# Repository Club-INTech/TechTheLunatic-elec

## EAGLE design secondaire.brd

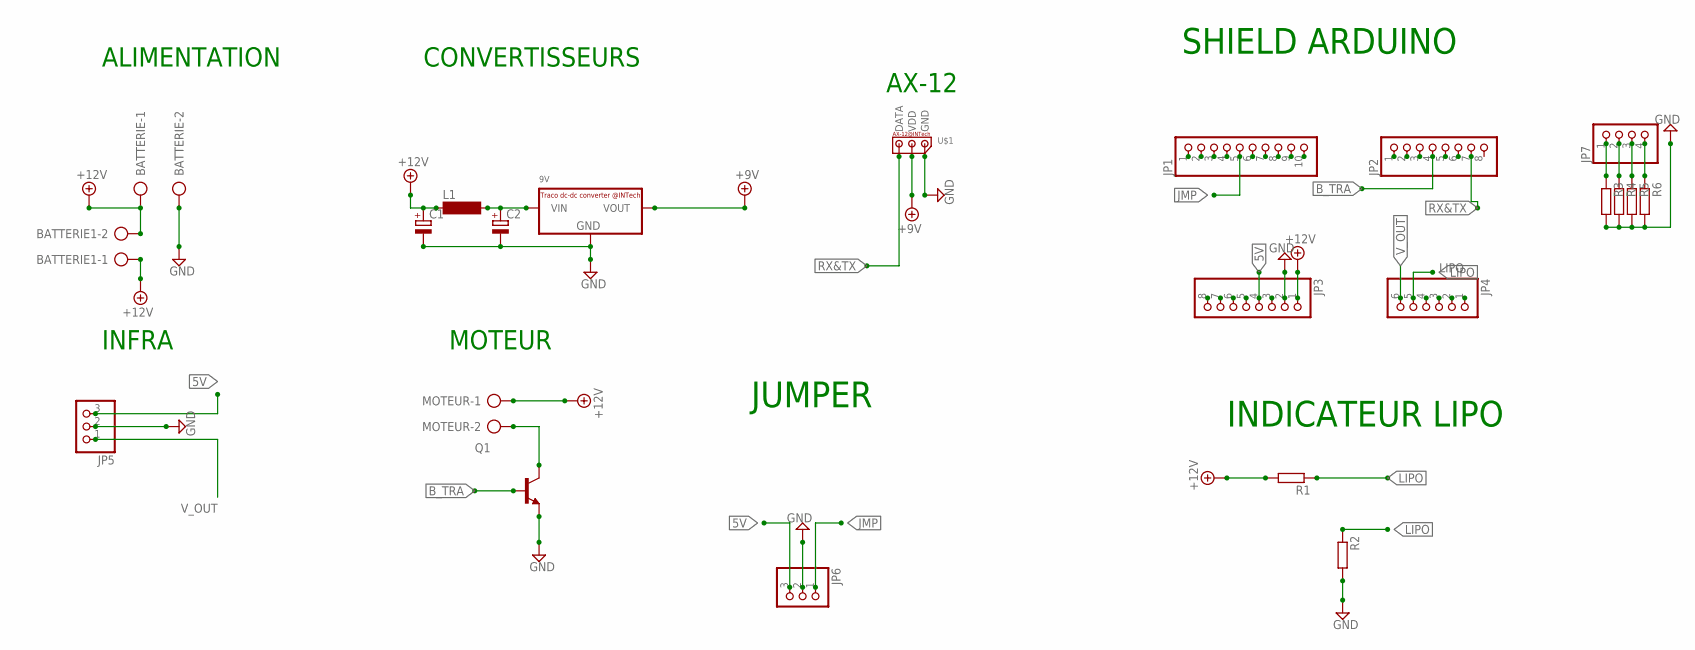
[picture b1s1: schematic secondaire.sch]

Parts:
9V: R-78C-1.0_INTECH; SIP3_INTECH
BATTERIE, BATTERIE1: AK300/2
C1, C2: CPOL-EUE2.5-6; E2,5-6
JP1: PINHD-1X10; 1X10
JP2, JP3: PINHD-1X8; 1X08
JP4: PINHD-1X6; 1X06
JP5, JP6: PINHD-1X3; 1X03
JP7: PINHD-1X4; 1X04
L1: SD12-1000; SD12_1000
MOTEUR: AK300/2
Q1: BC237-NPN-TO92-CBE; TO92-CBE
R1, R2, R3, R4, R5, R6: R-EU_0204/7; 0204/7
U$1: AX-12_CF_INTECH

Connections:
5V: JP3.4, JP5.3, JP6.3
+9V: 9V.VOUT, U$1.VDD
+12V: BATTERIE.1, BATTERIE1.1, BATTERIE1.2, C1.+, JP3.1, L1.1, MOTEUR.1, R1.2
B_TRA: JP2.4, Q1.B
COL: MOTEUR.2, Q1.C
GND: 9V.GND, BATTERIE.2, C1.-, C2.-, JP3.2, JP5.2, JP6.2, Q1.E, R2.2, R3.2, R4.2, R5.2, R6.2, U$1.GND
JMP: JP1.5, JP6.1
LIPO: JP4.5, R1.1, R2.1
unnamed: 9V.VIN, C2.+, L1.2
unnamed: JP7.1, R3.1
unnamed: JP7.2, R4.1
unnamed: JP7.3, R5.1
unnamed: JP7.4, R6.1
RX&TX: JP2.7, U$1.DATA
V_OUT: JP4.6, JP5.1

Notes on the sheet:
ALIMENTATION
CONVERTISSEURS
MOTEUR
AX-12
INFRA
JUMPER
SHIELD ARDUINO
INDICATEUR LIPO

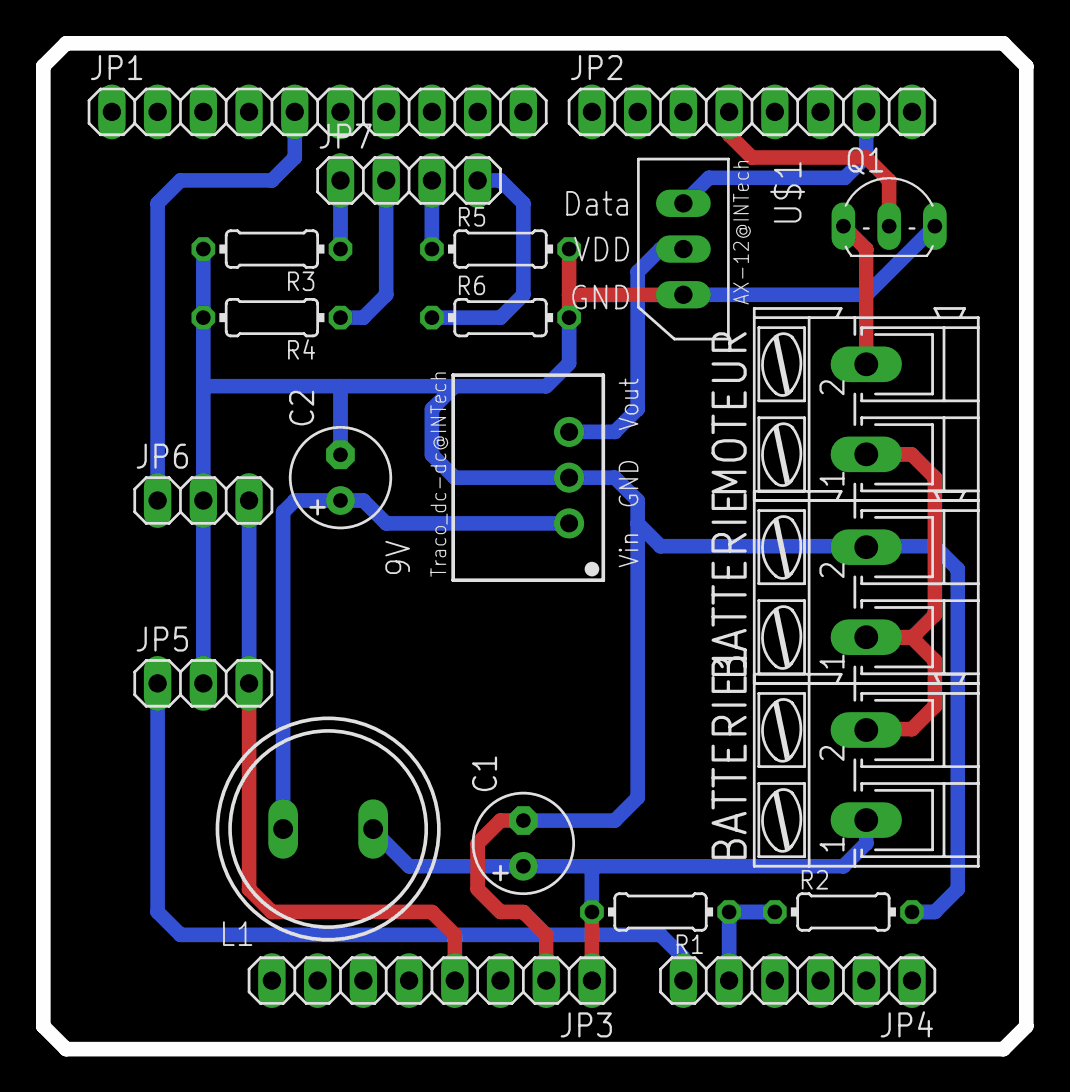
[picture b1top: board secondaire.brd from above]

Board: 2 copper layers, 54.6 x 55.9 mm, 22 parts (0 on the bottom side), 15 nets.

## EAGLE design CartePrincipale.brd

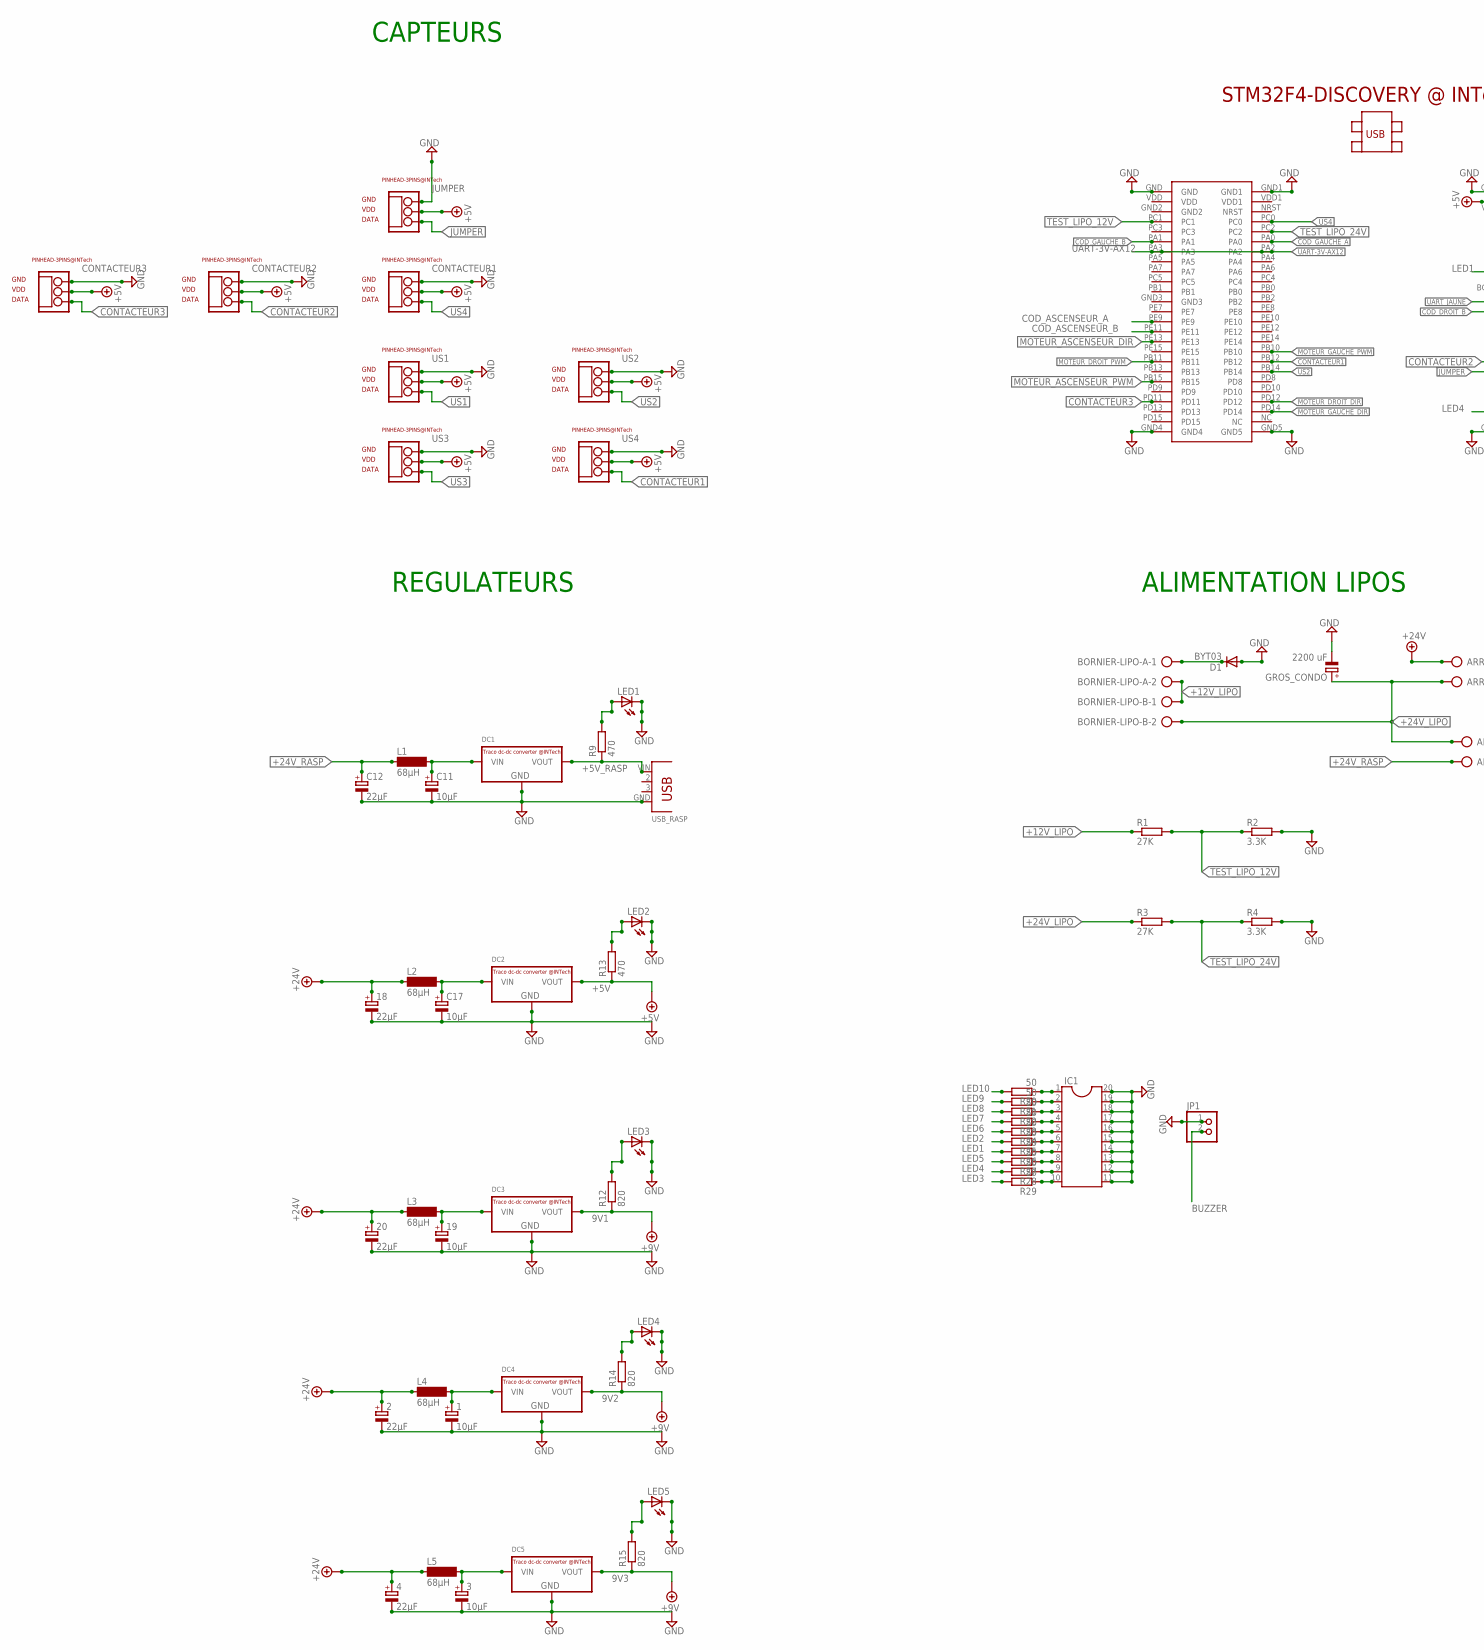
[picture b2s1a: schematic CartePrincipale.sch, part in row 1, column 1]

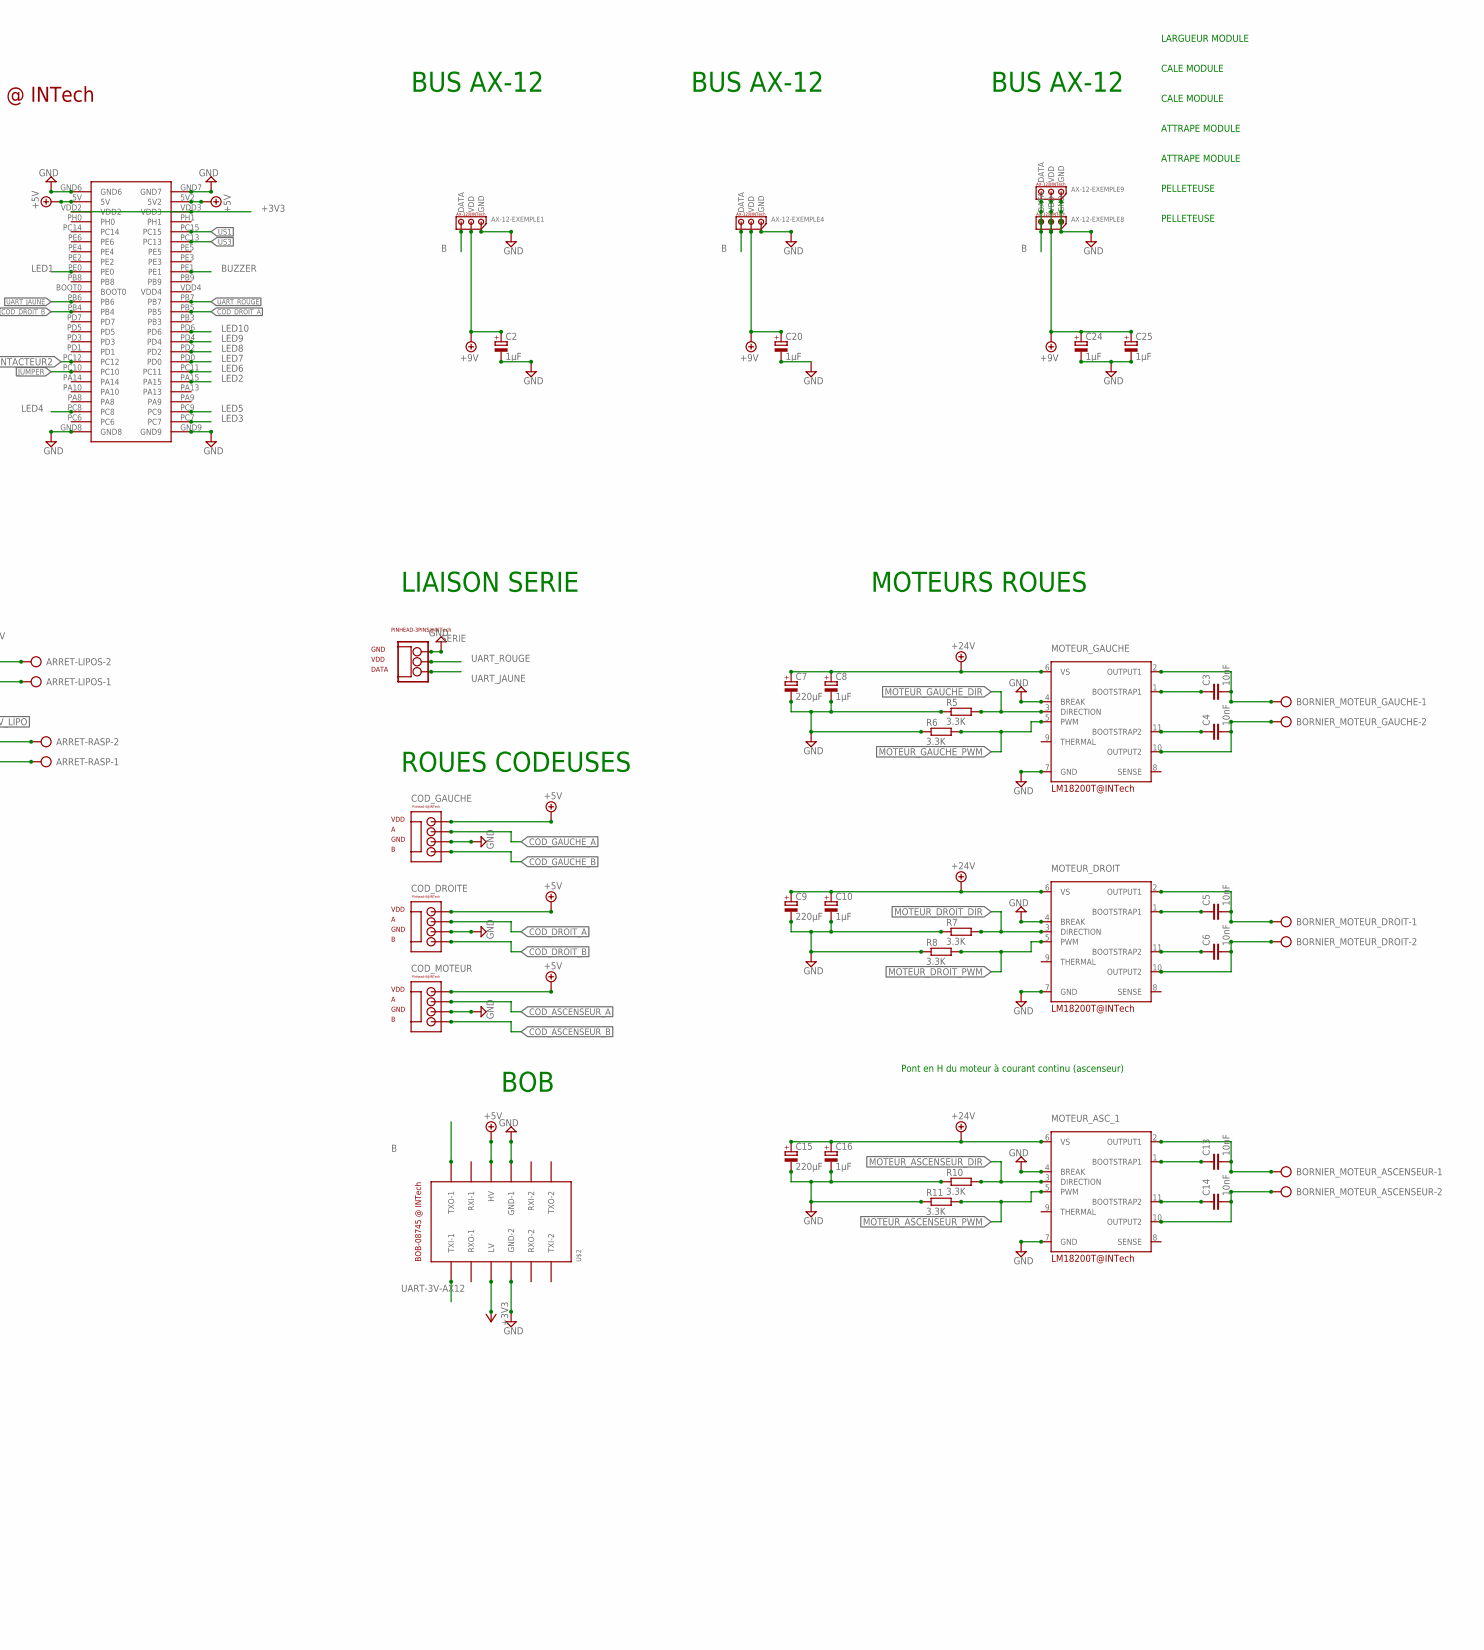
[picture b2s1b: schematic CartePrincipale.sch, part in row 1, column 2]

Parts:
1, 3, 19: 10µF; E2,5-6
2, 4, 18, 20: 22µF; E2,5-6
ARRET-LIPOS: AK300/2
ARRET-RASP: AK300/2
AX-12-EXEMPLE1, AX-12-EXEMPLE4, AX-12-EXEMPLE8, AX-12-EXEMPLE9: AX-12_CF_INTECH
BORNIER-LIPO-A: AK300/2
BORNIER-LIPO-B: AK300/2
BORNIER_MOTEUR_ASCENSEUR: AK300/2
BORNIER_MOTEUR_DROIT: AK300/2
BORNIER_MOTEUR_GAUCHE: AK300/2
C2, C20, C24, C25: 1µF; E2,5-6E
C3, C4, C5, C6, C13, C14: 10nF; C050-025X075
C7, C9, C15: 220µF; E3,5-8
C8, C10, C16: 1µF; E3,5-8
C11, C17: 10µF; E2,5-6
C12: 22µF; E2,5-6
COD_DROITE: PINHEAD-4_CF_INTECH
COD_GAUCHE: PINHEAD-4_CF_INTECH
COD_MOTEUR: PINHEAD-4_CF_INTECH
CONTACTEUR1, CONTACTEUR2, CONTACTEUR3: PINHEAD_CF_INTECH
D1: BYT03; DO27-15
DC1, DC2: 5V_1A; SIP3_INTECH
DC3, DC4, DC5: 9V_1A; SIP3_INTECH
GROS_CONDO: 2200 uF; EB20D
IC1: DIL20S; SOCKET-20
JP1: PINHD-1X2; 1X02
JUMPER: PINHEAD_CF_INTECH
L1, L2, L3, L4, L5: 68µH; SD12K100
LED1, LED2, LED3, LED4, LED5: LED5MM
MOTEUR_ASC_1: LM18200T_CF_INTECH
MOTEUR_DROIT: LM18200T_CF_INTECH
MOTEUR_GAUCHE: LM18200T_CF_INTECH
R1, R3: 27K; 0207/10
R2, R4, R5, R6, R7, R8, R10, R11: 3.3K; 0207/10
R9, R13: 470; 0207/10
R12, R14, R15: 820; 0207/10
R20, R21, R22, R23, R24, R25, R26, R27, R28, R29: 50; 0207/2V
SERIE: PINHEAD_CF_INTECH
U$1: STM32F4-DISCOVERY
U$2: BOB-08745
US1, US2, US3, US4: PINHEAD_CF_INTECH
USB_RASP: USB_87520; USB

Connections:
9V1: AX-12-EXEMPLE8.VDD, AX-12-EXEMPLE9.VDD, C24.+, C25.+, DC3.VOUT, R12.1
9V2: AX-12-EXEMPLE4.VDD, C20.+, DC4.VOUT, R14.1
9V3: AX-12-EXEMPLE1.VDD, C2.+, DC5.VOUT, R15.1
+3V3: U$1.VDD2, U$1.VDD3, U$2.LV
+5V: COD_DROITE.VDD, COD_GAUCHE.VDD, COD_MOTEUR.VDD, CONTACTEUR1.VDD, CONTACTEUR2.VDD, CONTACTEUR3.VDD, DC2.VOUT, JUMPER.VDD, R13.1, U$1.5V, U$1.5V2, U$2.HV, US1.VDD, US2.VDD, US3.VDD, US4.VDD
+5V_RASP: DC1.VOUT, R9.1, USB_RASP.VIN
+12V_LIPO: BORNIER-LIPO-A.2, BORNIER-LIPO-B.1, R1.1
+24V: 2.+, 4.+, 18.+, 20.+, ARRET-LIPOS.2, C7.+, C8.+, C9.+, C10.+, C15.+, C16.+, L2.1, L3.1, L4.1, L5.1, MOTEUR_ASC_1.6 (VS), MOTEUR_DROIT.6 (VS), MOTEUR_GAUCHE.6 (VS)
+24V_LIPO: ARRET-LIPOS.1, ARRET-RASP.2, BORNIER-LIPO-B.2, GROS_CONDO.+, R3.1
+24V_RASP: ARRET-RASP.1, C12.+, L1.1
B: AX-12-EXEMPLE1.DATA, AX-12-EXEMPLE4.DATA, AX-12-EXEMPLE8.DATA, AX-12-EXEMPLE9.DATA, U$2.TXO-1
BUZZER: JP1.2, U$1.PE1
COD_ASCENSEUR_A: COD_MOTEUR.A, U$1.PE9
COD_ASCENSEUR_B: COD_MOTEUR.B, U$1.PE11
COD_DROIT_A: COD_DROITE.A, U$1.PB5
COD_DROIT_B: COD_DROITE.B, U$1.PB4
COD_GAUCHE_A: COD_GAUCHE.A, U$1.PA0
COD_GAUCHE_B: COD_GAUCHE.B, U$1.PA1
CONTACTEUR1: U$1.PB12, US4.DATA
CONTACTEUR2: CONTACTEUR2.DATA, U$1.PC12
CONTACTEUR3: CONTACTEUR3.DATA, U$1.PD11
GND: 1.-, 2.-, 3.-, 4.-, 18.-, 19.-, 20.-, AX-12-EXEMPLE1.GND, AX-12-EXEMPLE4.GND, AX-12-EXEMPLE8.GND, AX-12-EXEMPLE9.GND, C2.-, C7.-, C8.-, C9.-, C10.-, C11.-, C12.-, C15.-, C16.-, C17.-, C20.-, C24.-, C25.-, COD_DROITE.GND, COD_GAUCHE.GND, COD_MOTEUR.GND, CONTACTEUR1.GND, CONTACTEUR2.GND, CONTACTEUR3.GND, D1.A, DC1.GND, DC2.GND, DC3.GND, DC4.GND, DC5.GND, GROS_CONDO.-, IC1.11, IC1.12, IC1.13, IC1.14, IC1.15, IC1.16, IC1.17, IC1.18, IC1.19, IC1.20, JP1.1, JUMPER.GND, LED1.K (C), LED2.K (C), LED3.K (C), LED4.K (C), LED5.K (C), MOTEUR_ASC_1.4 (BREAK), MOTEUR_ASC_1.7 (GND), MOTEUR_DROIT.4 (BREAK), MOTEUR_DROIT.7 (GND), MOTEUR_GAUCHE.4 (BREAK), MOTEUR_GAUCHE.7 (GND), R2.2, R4.2, R5.1, R6.1, R7.1, R8.1, R10.1, R11.1, SERIE.GND, U$1.GND, U$1.GND1, U$1.GND4, U$1.GND5, U$1.GND6, U$1.GND7, U$1.GND8, U$1.GND9, U$2.GND-1, U$2.GND-2, US1.GND, US2.GND, US3.GND, US4.GND, USB_RASP.GND
JUMPER: JUMPER.DATA, U$1.PC10
LED1: R26.2, U$1.PE0
LED2: R25.2, U$1.PA15
LED3: R29.2, U$1.PC7
LED4: R28.2, U$1.PC8
LED5: R27.2, U$1.PC9
LED6: R24.2, U$1.PC11
LED7: R23.2, U$1.PD0
LED8: R22.2, U$1.PD2
LED9: R21.2, U$1.PD4
LED10: R20.2, U$1.PD6
MOTEUR_ASCENSEUR_DIR: MOTEUR_ASC_1.3 (DIRECTION), R10.2, U$1.PE13
MOTEUR_ASCENSEUR_PWM: MOTEUR_ASC_1.5 (PWM), R11.2, U$1.PB15
MOTEUR_DROIT_DIR: MOTEUR_DROIT.3 (DIRECTION), R7.2, U$1.PD12
MOTEUR_DROIT_PWM: MOTEUR_DROIT.5 (PWM), R8.2, U$1.PB11
MOTEUR_GAUCHE_DIR: MOTEUR_GAUCHE.3 (DIRECTION), R5.2, U$1.PD14
MOTEUR_GAUCHE_PWM: MOTEUR_GAUCHE.5 (PWM), R6.2, U$1.PB10
unnamed: BORNIER-LIPO-A.1, D1.C
unnamed: C4.1, MOTEUR_GAUCHE.11 (BOOTSTRAP2)
unnamed: C3.1, MOTEUR_GAUCHE.1 (BOOTSTRAP1)
unnamed: C13.1, MOTEUR_ASC_1.1 (BOOTSTRAP1)
unnamed: C14.1, MOTEUR_ASC_1.11 (BOOTSTRAP2)
unnamed: BORNIER_MOTEUR_ASCENSEUR.1, C13.2, MOTEUR_ASC_1.2 (OUTPUT1)
unnamed: BORNIER_MOTEUR_ASCENSEUR.2, C14.2, MOTEUR_ASC_1.10 (OUTPUT2)
unnamed: 1.+, DC4.VIN, L4.2
unnamed: LED1.A, R9.2
unnamed: C5.1, MOTEUR_DROIT.1 (BOOTSTRAP1)
unnamed: C6.1, MOTEUR_DROIT.11 (BOOTSTRAP2)
unnamed: C11.+, DC1.VIN, L1.2
unnamed: C17.+, DC2.VIN, L2.2
unnamed: BORNIER_MOTEUR_GAUCHE.1, C3.2, MOTEUR_GAUCHE.2 (OUTPUT1)
unnamed: BORNIER_MOTEUR_GAUCHE.2, C4.2, MOTEUR_GAUCHE.10 (OUTPUT2)
unnamed: BORNIER_MOTEUR_DROIT.1, C5.2, MOTEUR_DROIT.2 (OUTPUT1)
unnamed: BORNIER_MOTEUR_DROIT.2, C6.2, MOTEUR_DROIT.10 (OUTPUT2)
unnamed: 19.+, DC3.VIN, L3.2
unnamed: 3.+, DC5.VIN, L5.2
unnamed: IC1.1, R20.1
unnamed: IC1.2, R21.1
unnamed: IC1.3, R22.1
unnamed: IC1.4, R23.1
unnamed: IC1.5, R24.1
unnamed: IC1.6, R25.1
unnamed: IC1.7, R26.1
unnamed: IC1.8, R27.1
unnamed: IC1.9, R28.1
unnamed: IC1.10, R29.1
unnamed: LED2.A, R13.2
unnamed: LED3.A, R12.2
unnamed: LED5.A, R15.2
unnamed: LED4.A, R14.2
TEST_LIPO_12V: R1.2, R2.1, U$1.PC1
TEST_LIPO_24V: R3.2, R4.1, U$1.PC2
UART-3V-AX12: U$1.PA2, U$1.PA3, U$2.TXI-1
UART_JAUNE: SERIE.DATA, U$1.PB6
UART_ROUGE: SERIE.VDD, U$1.PB7
US1: U$1.PC15, US1.DATA
US2: U$1.PB14, US2.DATA
US3: U$1.PC13, US3.DATA
US4: CONTACTEUR1.DATA, U$1.PC0

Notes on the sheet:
BUS AX-12
BOB
ALIMENTATION LIPOS
LIAISON SERIE
MOTEURS ROUES
ROUES CODEUSES
CAPTEURS
REGULATEURS
Pont en H du moteur à courant continu (ascenseur)
PELLETEUSE
ATTRAPE MODULE
CALE MODULE
LARGUEUR MODULE

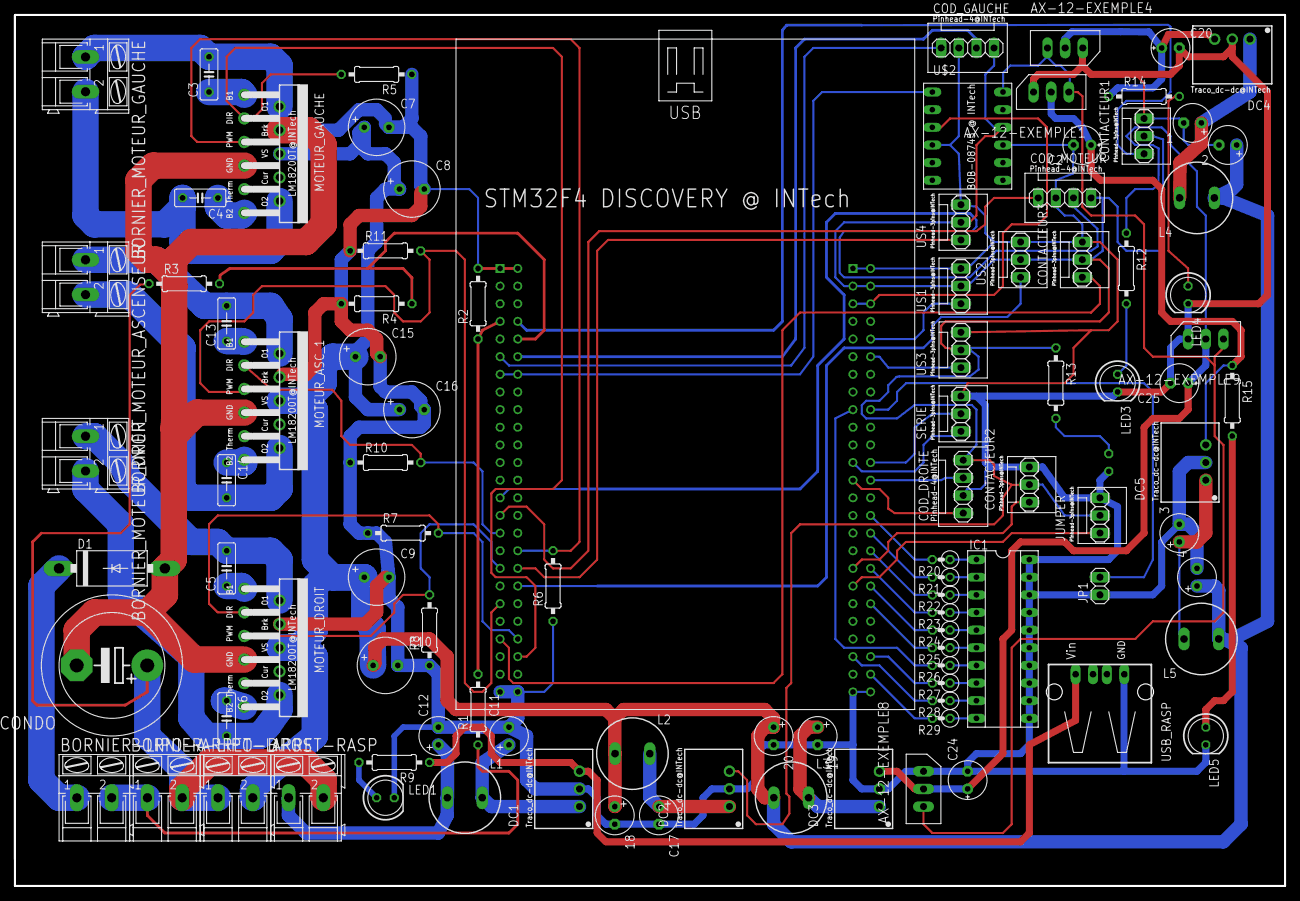
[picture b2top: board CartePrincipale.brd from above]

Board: 2 copper layers, 182.9 x 125.4 mm, 99 parts (1 on the bottom side), 81 nets.

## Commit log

2017-03-27 Ajout carte principale du robot
2017-03-27 test pour slack
2017-03-27 ajout du secondaire
2017-03-27 un gitignore / tentative de gitignore pour faire plaisir à PF
2017-03-27 si on git add avant, c'est mieux
2017-03-27 ceci est un commit
2017-03-27 ceci est un commit : le retour
2017-03-27 Ceci est un commit : la menace de la loli
2017-03-27 Ceci est un commit : la revanche du 1A
